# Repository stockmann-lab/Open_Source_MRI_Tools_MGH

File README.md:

# General lab resources

# Low-noise pre-amp

# Toroidal choke

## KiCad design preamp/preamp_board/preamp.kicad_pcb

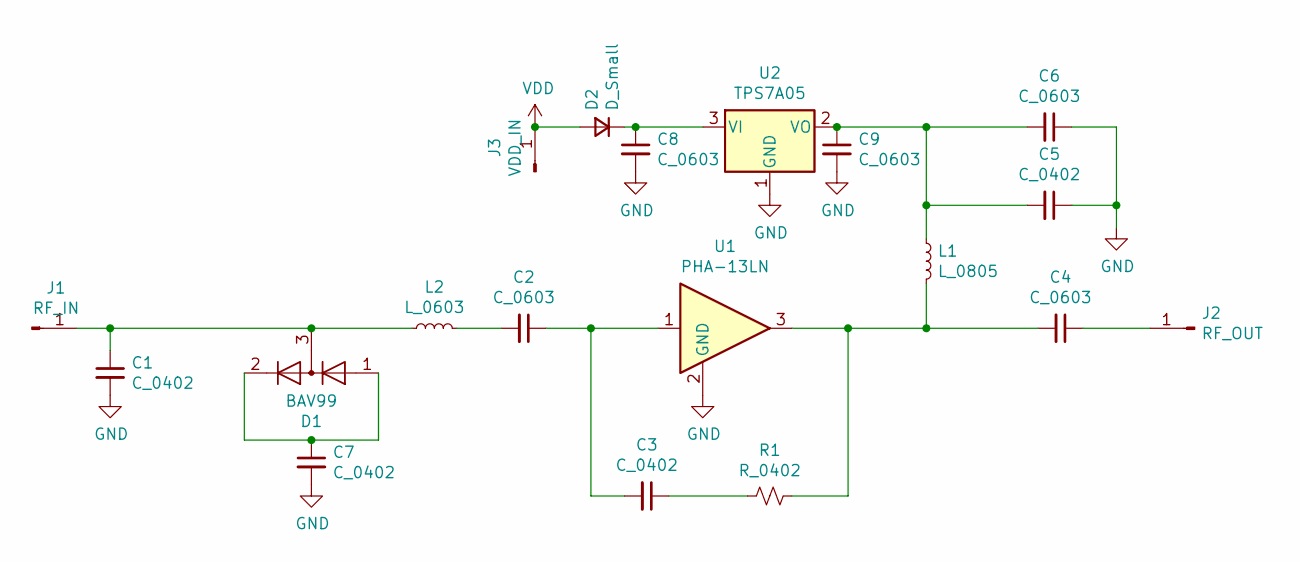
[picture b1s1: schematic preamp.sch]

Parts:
C1, C3, C5, C7: C_0402; C_0402_1005Metric
C2, C4, C6, C8, C9: C_0603; C_0603_1608Metric
D1: BAV99; SOT-23
D2: D_Small; D_SOD-323_HandSoldering
J1: RF_IN; TestPoint_Pad_1.0x1.0mm
J2: RF_OUT; TestPoint_Pad_1.0x1.0mm
J3: VDD_IN; TestPoint_Pad_1.0x1.0mm
L1: L_0805; L_0805_2012Metric
L2: L_0603; L_0603_1608Metric
R1: R_0402; R_0402_1005Metric
U1: PHA-13LN; SOT-89-3
U2: TPS7A05; SOT-23

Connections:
GND: C1.2, C5.1, C6.1, C7.2, C8.2, C9.2, U1.2 (GND), U2.1 (GND)
unnamed: C1.1, D1.3 (K), J1.1, L2.1
unnamed: C2.1, C3.2, U1.1
unnamed: C2.2, L2.2
unnamed: C3.1, R1.2
unnamed: C4.1, J2.1
unnamed: C4.2, L1.2, R1.1, U1.3
unnamed: C5.2, C6.2, C9.1, L1.1, U2.2 (VO)
unnamed: C7.1, D1.1 (K), D1.2 (A)
unnamed: C8.1, D2.1 (K), U2.3 (VI)
VDD: D2.2 (A), J3.1

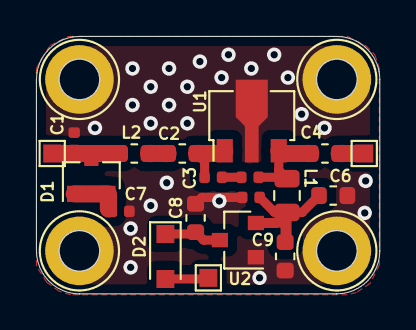
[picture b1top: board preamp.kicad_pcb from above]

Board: 2 copper layers, 19.0 x 14.3 mm, 19 parts (0 on the bottom side), 11 nets.

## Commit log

2020-07-29 Added preamp files
2020-07-30 Added choke folder and test data
2020-08-03 Added 3T design and FEKO data
2020-08-03 Readme for chokes added
2020-08-03 Readme adjustments
2020-08-03 Readme adjustments pt.2
2020-08-03 Added images and reorganized data
2020-08-10 Documenting amplifier comparisons, S11 and S21 documentation needs revision
2020-08-10 Cleaning up the folder to include just necessary files
2021-01-14 ODU female v1 model
